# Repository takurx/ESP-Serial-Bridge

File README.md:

# ESP32-Serial-Bridge, ESP32S3-Serial-Bridge, 3 port concurrent

---

# Takurx's Notes

## Project Overview

This repository is a fork of [AlphaLima/ESP32-Serial-Bridge](https://github.com/AlphaLima/ESP32-Serial-Bridge) (via [Yuri's fork](https://github.com/yuri-rage/ESP32-Serial-Bridge)).  
It provides a transparent WiFi (TCP/UDP) ↔ multi-UART bridge, targeting both ESP32 and **ESP32-S3** boards.

In addition to the original/Yuri functionality, this fork adds:

- ESP32-S3 (PlatformIO) support for Bridge (Host) and Client
- 3-UART concurrent client (`Kerberos`)
- Hardware flow control (CTS/RTS) pin definitions
- Buffer size tuning for high-throughput stability
- Non-blocking TX with pending queue
- PCB design (KiCad) for ESP32 and ESP32-S3
- 3D-printable enclosure STL files
- Speed test scripts and result logs

---

## Repository Structure

```
ESP-Serial-Bridge/
├── ESP-Serial-Bridge/                        # Original Arduino IDE sketch (ESP32/ESP8266)
│   ├── ESP-Serial-Bridge.ino
│   └── config.h
│
├── ESP32-Serial-WiFi-Client/                 # Arduino IDE single-UART TCP/UDP Client (Yuri)
│   ├── ESP32-Serial-WiFi-Client.ino
│   └── client_config.h
│
├── ESP32-Serial-WiFi-Client-Kerberos/        # Arduino IDE 3-UART concurrent Client (ESP32)
│   ├── ESP32-Serial-WiFi-Client-Kerberos.ino
│   └── client_config.h
│
├── pio-ESP32S3-Serial-WiFi-Bridge/           # PlatformIO Bridge (Host) for ESP32-S3
│   ├── src/main.cpp
│   ├── include/config.h
│   └── platformio.ini
│
├── pio-ESP32S3-Serial-WiFi-Client-Kerberos/  # PlatformIO 3-UART Client (Kerberos) for ESP32-S3
│   ├── src/main.cpp
│   ├── include/client_config.h
│   └── platformio.ini
│
├── pcb_kicad/
│   ├── esp_serial_bridge_pcb/                # KiCad PCB for ESP32
│   └── esp32s3_serial_bridge_pcb/            # KiCad PCB for ESP32-S3 (Kerberos)
│
├── case_3dprint/                             # 3D-printable enclosure STL files
├── speed_test_script/                        # Python speed-test scripts and result logs
└── README.md
```

---

## Recent Updates (Takurx)

### English

#### **Near Full-Speed 3-Port Operation Achieved (Jun 2026)**
Applied buffer optimizations (developed for the Bridge/Host) to the Client (Kerberos) side.  
Result: all three UARTs now operate at **≈ 110,000–115,200 bps** in both directions simultaneously.

- Host → Client (×3 ports): ≈ **110,000 bps** (previously ≈ 13,000 bps)
- Client → Host (×3 ports): ≈ **115,200 bps** (stable)

Key changes:
- `setRxBufferSize(4096)` / `setTxBufferSize(4096)` applied to all UART ports before `begin()`
- Non-blocking TX: `availableForWrite()` used to avoid blocking `write()` calls
- Overflow data stored in a per-channel `txPendingBuf[]` queue and flushed next loop
- Bulk TCP read using `readBytes()` instead of byte-by-byte loop

#### **Buffer Separation: SOFTWAREBUFFERSIZE / HARDWAREBUFFERSIZE (Jun 2026)**
Separated buffer constant into two named constants in `config.h` for clarity:

| Constant | Size | Role |
|---|---|---|
| `HARDWAREBUFFERSIZE` | 4096 B | HardwareSerial internal ring buffer (ISR ← UART FIFO) |
| `SOFTWAREBUFFERSIZE` | 1024 B | Application working buffer (`buf1`, `buf2`, `txPending`) |

Data flow:
```
[UART RX] UART HW FIFO (1024B) → HardwareSerial ring buffer (4096B) → buf2[1024B] → TCP TX
[TCP RX]  TCP RX buffer (lwIP) → buf1[1024B] → HardwareSerial TX ring buffer (4096B) → UART TX
```

#### **pio-ESP32S3-Serial-WiFi-Client-Kerberos — 3-UART PlatformIO Client (Apr 2026)**
Added a PlatformIO version of the 3-UART concurrent client for ESP32-S3.  
Mirrors the same buffer/non-blocking approach as the Bridge Host side.

#### **PCB Design (KiCad) (Mar 2026)**
Added KiCad PCB designs (schematic + layout + Gerber) for:
- `esp_serial_bridge_pcb` — for ESP32 modules
- `esp32s3_serial_bridge_pcb` — for ESP32-S3 modules (Kerberos)

#### **pio-ESP32S3-Serial-WiFi-Bridge — ESP32-S3 PlatformIO Port (Feb 2026)**
New PlatformIO project targeting **RYMCU ESP32-S3-DevKitC-1** (board: `rymcu-esp32-s3-devkitc-1`).

Notable changes from original:
- All 3 UART ports configured with CTS/RTS pins (flow control disabled by default, can be enabled)
- `HARDWAREBUFFERSIZE` = 4096 bytes applied via `setRxBufferSize()` / `setTxBufferSize()`
- Non-blocking TX pending queue (`txPending[]`, `txPendingLen[]`) per UART port
- Bulk TCP read with `readBytes()` instead of 1-byte-at-a-time loop
- Hostname changed to `ESP32-S3`

#### **3-UART Concurrent Client — "Kerberos" (Feb 2026)**
Added `ESP32-Serial-WiFi-Client-Kerberos` (Arduino IDE) and its PlatformIO equivalent.  
Establishes three simultaneous TCP connections (one per UART) to the Bridge Host.

#### **Speed Test Results Summary**

| Date | Config | Host → Client | Client → Host |
|---|---|---|---|
| Dec 2025 | ESP32 AP mode, 1 port, flow ctrl None | ≈ 13,000 bps (drops to 7,000) | ≈ 100,000 bps (stable) |
| Feb 2026 | ESP32-S3 ↔ ESP32-S3, 1 port, flow ctrl ON | avg ≈ 82,000 bps | avg ≈ 20,000 bps |
| Feb 2026 | ESP32-S3 ↔ ESP32-S3, 1 port, flow ctrl OFF | avg ≈ 50,000 bps | avg ≈ 20,000 bps |
| Feb 2026 | ESP32-S3 ↔ ESP32-S3, 3 ports, flow ctrl None | 600–45,000 bps | 7,000–13,000 bps |
| Feb 2026 | 3 ports, flow ctrl ON/OFF | ≈ 13,000 bps avg | ≈ 10,000 bps avg |
| **Jun 2026** | **3 ports, buffer opt. applied to client**, flow ctrl None | **≈ 110,000 bps** | **≈ 115,200 bps** |

#### **Watch Dog Timer Bug Fix (Dec 2025)**
Fixed a critical bug where the system would enter an infinite loop when the Host side crashed and the Watch Dog Timer failed to activate. Now properly handles three scenarios:
1. Client-side crash (Client Reset) → Recovers with input from Host side
2. Host-side crash with quick recovery (Host Reset) → System continues normally
3. Host-side crash without recovery (Host OFF) → Client automatically resets every 30 seconds via Watch Dog Timer

#### **3D-Printable Case (Dec 2025)**
Added STL files for 3D-printable enclosure (box and cover, including v2 versions).

---

### 日本語

#### **3ポート同時フルスピード動作を達成 (2026年6月)**
Bridge（Host）側で開発したバッファ最適化手法をClient（Kerberos）側にも適用。  
全3ポートで**約110,000〜115,200 bps**の双方向同時通信が可能になった。

- Host → Client（×3ポート）: 約 **110,000 bps**（以前は約13,000 bps）
- Client → Host（×3ポート）: 約 **115,200 bps**（安定）

主な変更点：
- `setRxBufferSize(4096)` / `setTxBufferSize(4096)` を全UARTポートの `begin()` 前に適用
- 非ブロッキングTX: `availableForWrite()` でブロッキング `write()` を回避
- 書けなかったデータをポートごとの `txPendingBuf[]` キューに退避し次ループで再送
- TCPの一括読み出し（`readBytes()`）で1バイトずつのループを排除

#### **バッファ定数の分離: SOFTWAREBUFFERSIZE / HARDWAREBUFFERSIZE (2026年6月)**
`config.h` のバッファ定数を2つに分離して明確化：

| 定数 | サイズ | 役割 |
|---|---|---|
| `HARDWAREBUFFERSIZE` | 4096 B | HardwareSerial内部リングバッファ（ISR ← UART FIFO） |
| `SOFTWAREBUFFERSIZE` | 1024 B | アプリ作業バッファ（`buf1`, `buf2`, `txPending`） |

#### **pio-ESP32S3-Serial-WiFi-Client-Kerberos — 3UART PlatformIOクライアント (2026年4月)**
ESP32-S3向け3UART同時クライアントのPlatformIO版を追加。  
BridgeHost側と同じバッファ/非ブロッキング手法を適用。

#### **PCB設計（KiCad）(2026年3月)**
以下のKiCad PCB設計（回路図 + レイアウト + Gerber）を追加：
- `esp_serial_bridge_pcb` — ESP32モジュール用
- `esp32s3_serial_bridge_pcb` — ESP32-S3モジュール（Kerberos）用

#### **pio-ESP32S3-Serial-WiFi-Bridge — ESP32-S3 PlatformIO移植 (2026年2月)**
ESP32-S3（RYMCU ESP32-S3-DevKitC-1）向けの新しいPlatformIOプロジェクト。

主な変更点：
- 全3 UARTポートにCTS/RTSピンを定義（デフォルトはフロー制御無効）
- `HARDWAREBUFFERSIZE` = 4096バイトをRX/TXバッファ両方に適用
- ポートごとの非ブロッキング送信保留キュー（`txPending[]`）を実装
- TCP一括読み出しに変更（`readBytes()` 使用）
- ホスト名を `ESP32-S3` に変更

#### **3UART同時クライアント「Kerberos」(2026年2月)**
3つのTCP接続を同時確立するクライアント `ESP32-Serial-WiFi-Client-Kerberos`（Arduino IDE版）とそのPlatformIO版を追加。

#### **速度テスト結果サマリ**

| 日付 | 構成 | Host → Client | Client → Host |
|---|---|---|---|
| 2025年12月 | ESP32 APモード、1ポート、フロー制御なし | 約13,000 bps（時々7,000に低下） | 約100,000 bps（安定） |
| 2026年2月 | ESP32-S3同士、1ポート、フロー制御あり | 平均 約82,000 bps | 平均 約20,000 bps |
| 2026年2月 | ESP32-S3同士、1ポート、フロー制御なし | 平均 約50,000 bps | 平均 約20,000 bps |
| 2026年2月 | ESP32-S3同士、3ポート同時、フロー制御なし | 600〜45,000 bps | 7,000〜13,000 bps |
| 2026年2月 | 3ポート、フロー制御あり/なし | 平均 約13,000 bps | 平均 約10,000 bps |
| **2026年6月** | **3ポート、クライアント側バッファ最適化適用後**、フロー制御なし | **約110,000 bps** | **約115,200 bps** |

#### **Watch Dog Timer バグ修正 (2025年12月)**
Host側が落ちた時に無限ループに陥り、Watch Dog Timerが効かなかった重大なバグを修正。以下の3つのケースに対応:
1. Client側が落ちた場合（ClientのReset）→ Host側からの入力で回復
2. Host側が落ちてすぐ回復した場合（HostのReset）→ 正常動作
3. Host側が落ちて回復しない場合（HostのOFF）→ 30秒ごとにWatch Dog TimerでClientを自動Reset

#### **3Dプリント用ケース (2025年12月)**
3Dプリント可能なケースのSTLファイルを追加（ボックスとカバー、v2バージョンを含む）。

---

## Hardware: ESP32-S3 Pin Assignment

### Bridge Host (`pio-ESP32S3-Serial-WiFi-Bridge`)

| Port | RX Pin | TX Pin | CTS Pin | RTS Pin | TCP Port | UDP Port |
|---|---|---|---|---|---|---|
| COM0 | GPIO1 | GPIO43 | GPIO16 | GPIO15 | 8880 | 14550 |
| COM1 | GPIO18 | GPIO17 | GPIO10 | GPIO9  | 8881 | 14551 |
| COM2 | GPIO38 | GPIO37 | GPIO36 | GPIO35 | 8882 | 14552 |

- Static IP (AP mode): `192.168.4.1`
- Default SSID: `ssid_esp_uart_bridge3x3`
- Hardware flow control: pins defined, **disabled by default** (comment in code to enable)

---

# Yuri's Notes

This fork is compatible with both the ESP32 and ESP8266.

Because the ESP8266 has some idiosyncrasies with its hardware serial ports, I used SoftwareSerial to implement the ESP8266 bridge.  It is limited to ~115200 baud and will likely prove less reliable than an ESP32. `BLUETOOTH` (hardware limitation) and `PROTOCOL_UDP` (software limitation) are not available on the ESP8266.

As is, the sketch will compile, build, and upload without errors for the ESP32.  Edit `config.h` to configure and build for ESP8266.

There are many configurable parameters in `config.h`. Edit to suit your needs - inline comments should provide clarity.

## Major update, Apr 2023:
* Fixed compatibility with Arduino framework 2.0
* Added compatibility with PlatformIO.
* Implemented `PROTOCOL_UDP` (UDP broadcast)
* `PROTOCOL_TCP` and `PROTOCOL_UDP` can be used simultaneously, though doing so may result in serial traffic conflicts if your client connections are not managed carefully.
* Added `ESP32-Serial-WiFi-Client.ino` in a separate sketch folder to make an ESP32 TCP or UDP client that connects to the ESP-Serial-Bridge. Edit `client_config.h` and upload to a second board.
* Multiple bugs (possible buffer overruns) are fixed in the latest commit(s).
* Latest commits also include some styling/readability edits, though I can easily admit that it isn't the "prettiest" of C++ projects.

---

# ESP32-Serial-Bridge (Original by AlphaLima)

Transparent WiFi (TCP) to all three UART Bridge, supports both AP and STATION WiFi modes. The .ino file is the code for the ESP32. Use Arduino IDE for ESP32 to compile and upload it to the ESP32.
I made this project in order to connect Flight equipment devices devices like (Radio, Vario FLARM), to a Flight Computer (Kobo, Smartphones etc.),  but it is not limited to that. You can use it wherever you want, but on your own risk. Read license file for more details.                                  

===============================================================

Used Libraries: (must be installed in the arduino IDE):

https://github.com/espressif/arduino-esp32

===============================================================

In some cases the memorylayout is to small for this scetch.
If you face this problem you can either disable Bluetooth by removing
#define BLUETOOTH
in config.h 
or change the partition size as described here:
https://desire.giesecke.tk/index.php/2018/04/20/change-partition-size-arduino-ide/

Arduino hardware configuration:

https://github.com/AlphaLima/ESP32-Serial-Bridge/blob/master/Settings.jpg

===============================================================

example usecases:

https://www.youtube.com/watch?v=K2Hia06IMtk

https://www.youtube.com/watch?v=GoSxlQvuAhg

# Hardware (Original ESP32)
here is the wiring diagram recomendation:
https://raw.githubusercontent.com/AlphaLima/ESP32-Serial-Bridge/master/ESP32-SerialBridge.jpg             
Pinning                                                                                     
COM0 Rx <-> GPIO21                                                                               
COM0 Tx <-> GPIO01                                                                                 
COM1 Rx <-> GPIO16                                                                               
COM1 Tx <-> GPIO17                                                                              
COM2 Rx <-> GPIO15                                                                               
COM2 Tx <-> GPIO04                                                                              

NOTE: The PIN assignment has changed and may not look straigt forward (other PINs are marke as Rx/Tx), but this assignment allows to flash via USB also with hooked MAX3232 serial drivers.

I recomend to start your project with a Node32s or compatible evaluation board. For a TTL to RS232 level conversion search google for "TTL RS3232 Converter"

https://tech.scargill.net/wp-content/uploads/2017/05/ESP326.jpg

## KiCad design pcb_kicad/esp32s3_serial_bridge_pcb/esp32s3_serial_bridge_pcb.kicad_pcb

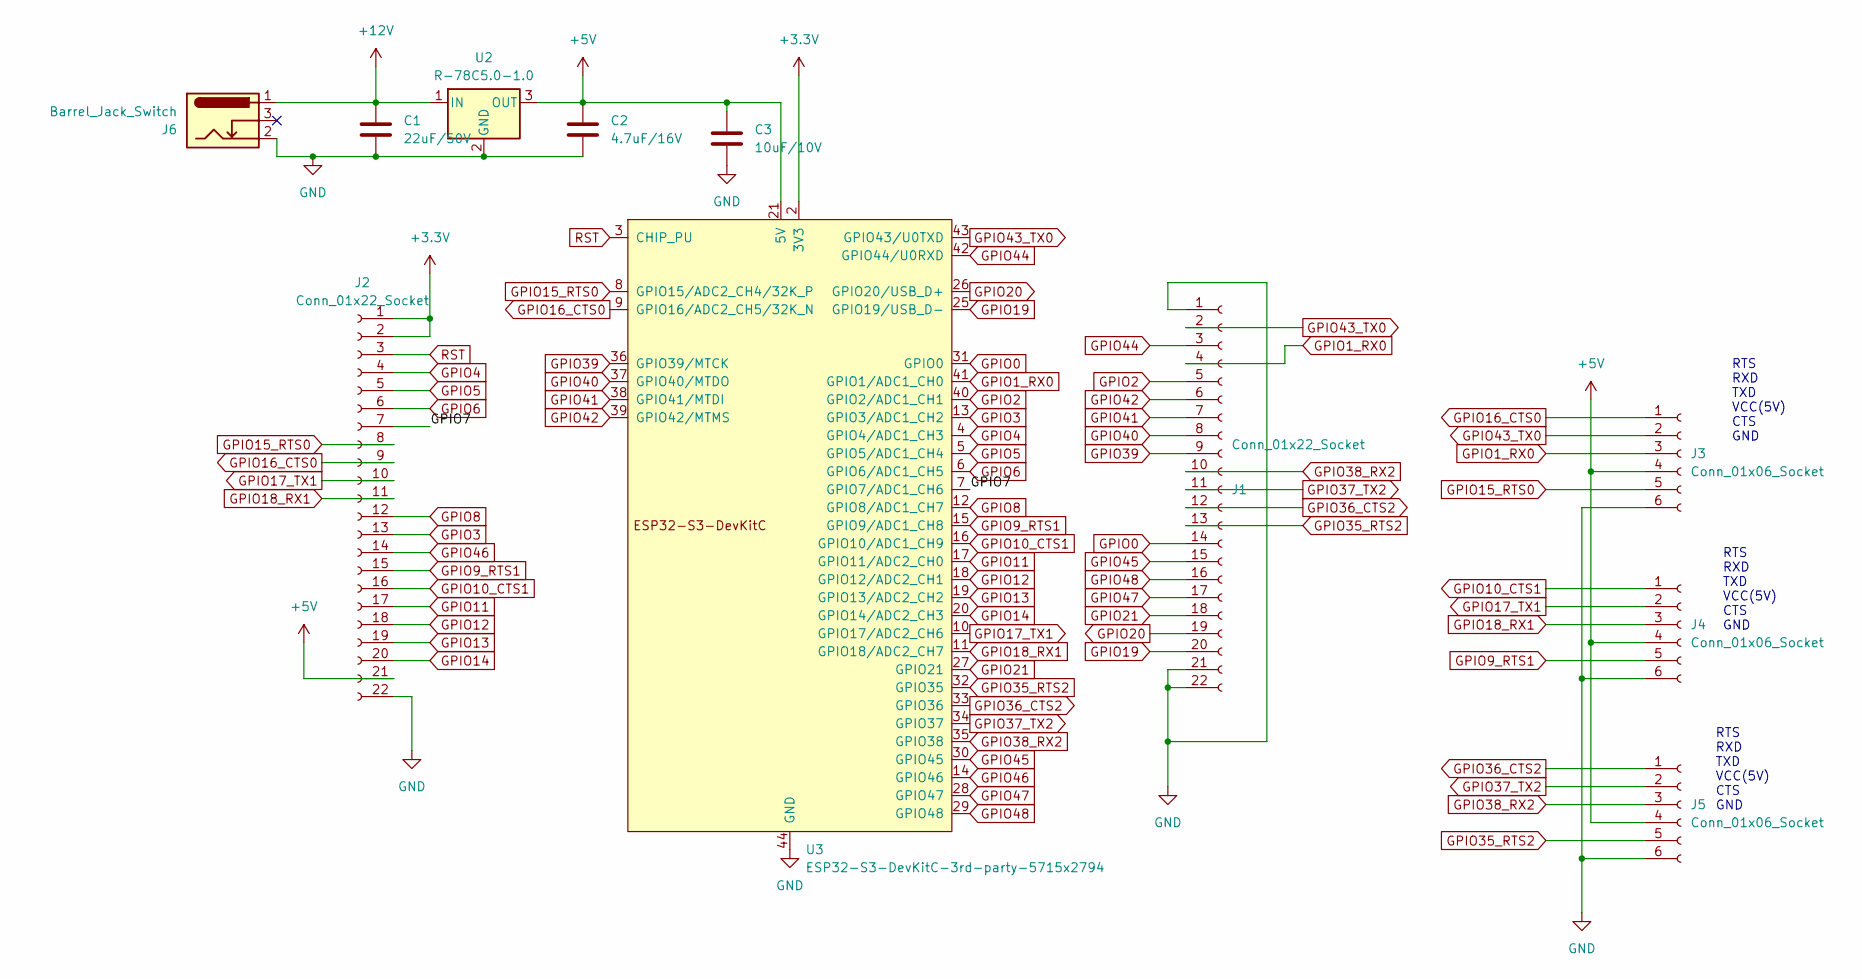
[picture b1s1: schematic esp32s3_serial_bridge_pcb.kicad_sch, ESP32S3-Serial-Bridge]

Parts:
C1: 22uF/50V; C_2220_5750Metric_Pad1.97x5.40mm_HandSolder
C2: 4.7uF/16V; C_1210_3225Metric_Pad1.33x2.70mm_HandSolder
C3: 10uF/10V; C_1210_3225Metric_Pad1.33x2.70mm_HandSolder
J1, J2: Conn_01x22_Socket; PinHeader_1x22_P2.54mm_Vertical
J3, J4, J5: Conn_01x06_Socket; PinHeader_1x06_P2.54mm_Vertical
J6: Barrel_Jack_Switch; BarrelJack_Horizontal
U2: R-78C5.0-1.0; Converter_DCDC_RECOM_R-78E-0.5_THT
U3: ESP32-S3-DevKitC-3rd-party-5715x2794; ESP32-S3-DevKitC_3rd_party_5715x2794

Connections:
+3.3V: J2.1, J2.2, U3.1 (3V3), U3.2 (3V3)
+5V: C2.1, C3.1, J2.21, J3.4, J4.4, J5.4, U2.3 (OUT), U3.21 (5V)
+12V: C1.1, J6.1, U2.1 (IN)
/GPIO7: J2.7, U3.7 (GPIO7/ADC1_CH6)
GND: C1.2, C2.2, C3.2, J1.1, J1.21, J1.22, J2.22, J3.6, J4.6, J5.6, J6.2, U2.2 (GND), U3.22 (GND), U3.23 (GND), U3.24 (GND), U3.44 (GND)
GPIO0: J1.14, U3.31 (GPIO0)
GPIO1_RX0: J1.4, J3.3, U3.41 (GPIO1/ADC1_CH0)
GPIO2: J1.5, U3.40 (GPIO2/ADC1_CH1)
GPIO3: J2.13, U3.13 (GPIO3/ADC1_CH2)
GPIO4: J2.4, U3.4 (GPIO4/ADC1_CH3)
GPIO5: J2.5, U3.5 (GPIO5/ADC1_CH4)
GPIO6: J2.6, U3.6 (GPIO6/ADC1_CH5)
GPIO8: J2.12, U3.12 (GPIO8/ADC1_CH7)
GPIO9_RTS1: J2.15, J4.5, U3.15 (GPIO9/ADC1_CH8)
GPIO10_CTS1: J2.16, J4.1, U3.16 (GPIO10/ADC1_CH9)
GPIO11: J2.17, U3.17 (GPIO11/ADC2_CH0)
GPIO12: J2.18, U3.18 (GPIO12/ADC2_CH1)
GPIO13: J2.19, U3.19 (GPIO13/ADC2_CH2)
GPIO14: J2.20, U3.20 (GPIO14/ADC2_CH3)
GPIO15_RTS0: J2.8, J3.5, U3.8 (GPIO15/ADC2_CH4/32K_P)
GPIO16_CTS0: J2.9, J3.1, U3.9 (GPIO16/ADC2_CH5/32K_N)
GPIO17_TX1: J2.10, J4.2, U3.10 (GPIO17/ADC2_CH6)
GPIO18_RX1: J2.11, J4.3, U3.11 (GPIO18/ADC2_CH7)
GPIO19: J1.20, U3.25 (GPIO19/USB_D-)
GPIO20: J1.19, U3.26 (GPIO20/USB_D+)
GPIO21: J1.18, U3.27 (GPIO21)
GPIO35_RTS2: J1.13, J5.5, U3.32 (GPIO35)
GPIO36_CTS2: J1.12, J5.1, U3.33 (GPIO36)
GPIO37_TX2: J1.11, J5.2, U3.34 (GPIO37)
GPIO38_RX2: J1.10, J5.3, U3.35 (GPIO38)
GPIO39: J1.9, U3.36 (GPIO39/MTCK)
GPIO40: J1.8, U3.37 (GPIO40/MTDO)
GPIO41: J1.7, U3.38 (GPIO41/MTDI)
GPIO42: J1.6, U3.39 (GPIO42/MTMS)
GPIO43_TX0: J1.2, J3.2, U3.43 (GPIO43/U0TXD)
GPIO44: J1.3, U3.42 (GPIO44/U0RXD)
GPIO45: J1.15, U3.30 (GPIO45)
GPIO46: J2.14, U3.14 (GPIO46)
GPIO47: J1.17, U3.28 (GPIO47)
GPIO48: J1.16, U3.29 (GPIO48)
RST: J2.3, U3.3 (CHIP_PU)

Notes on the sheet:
RTS RXD TXD VCC(5V) CTS GND

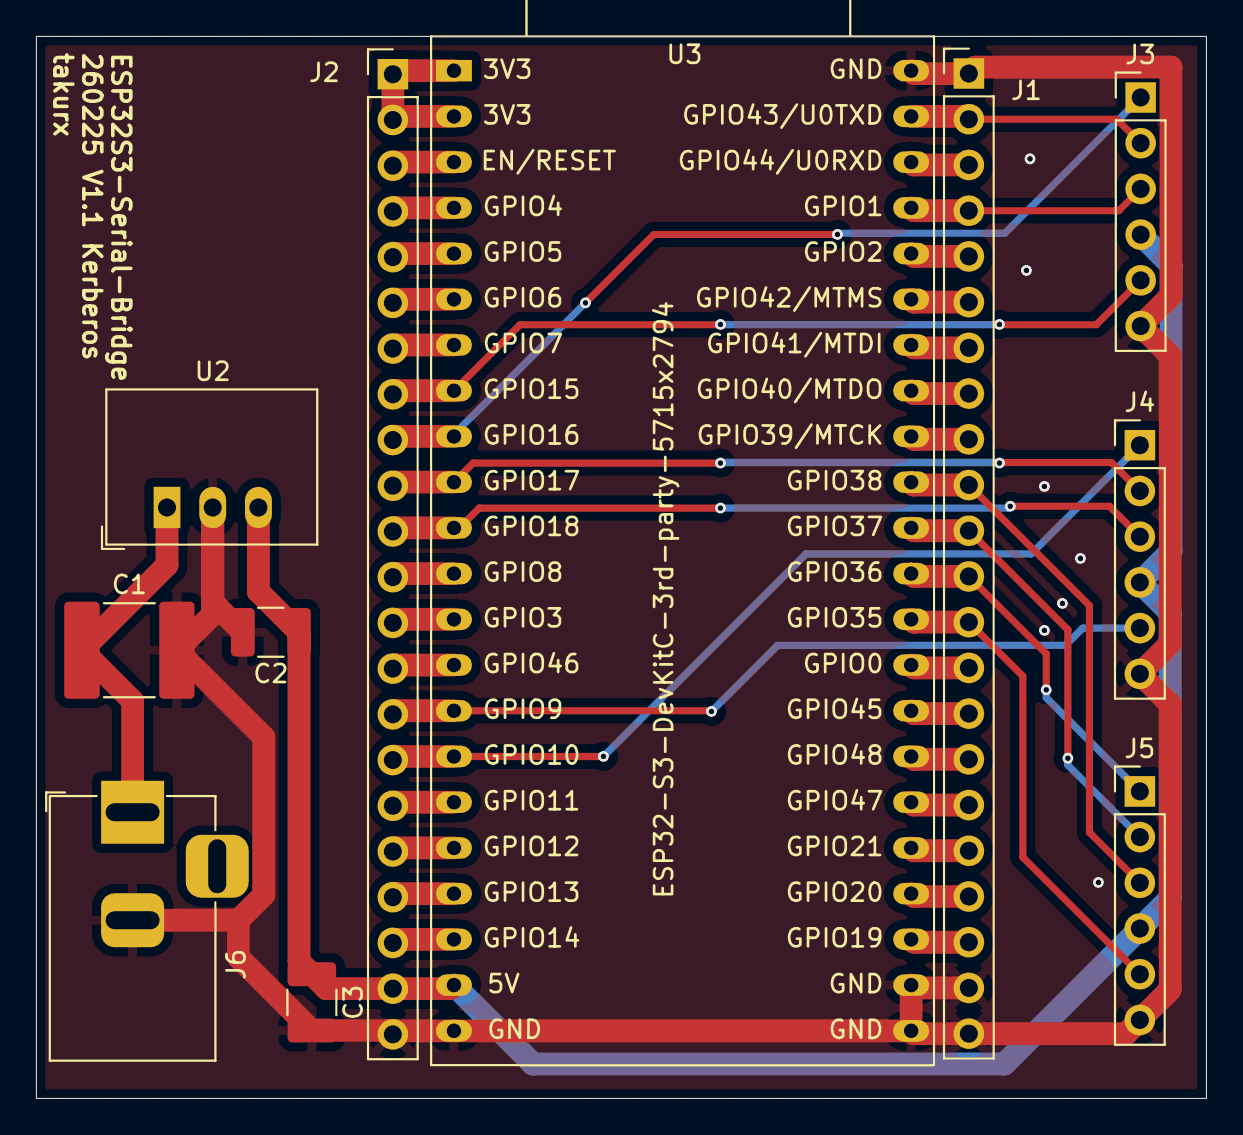
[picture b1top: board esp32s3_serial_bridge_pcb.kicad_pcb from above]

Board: 2 copper layers, 65.0 x 59.0 mm, 11 parts (0 on the bottom side), 41 nets.

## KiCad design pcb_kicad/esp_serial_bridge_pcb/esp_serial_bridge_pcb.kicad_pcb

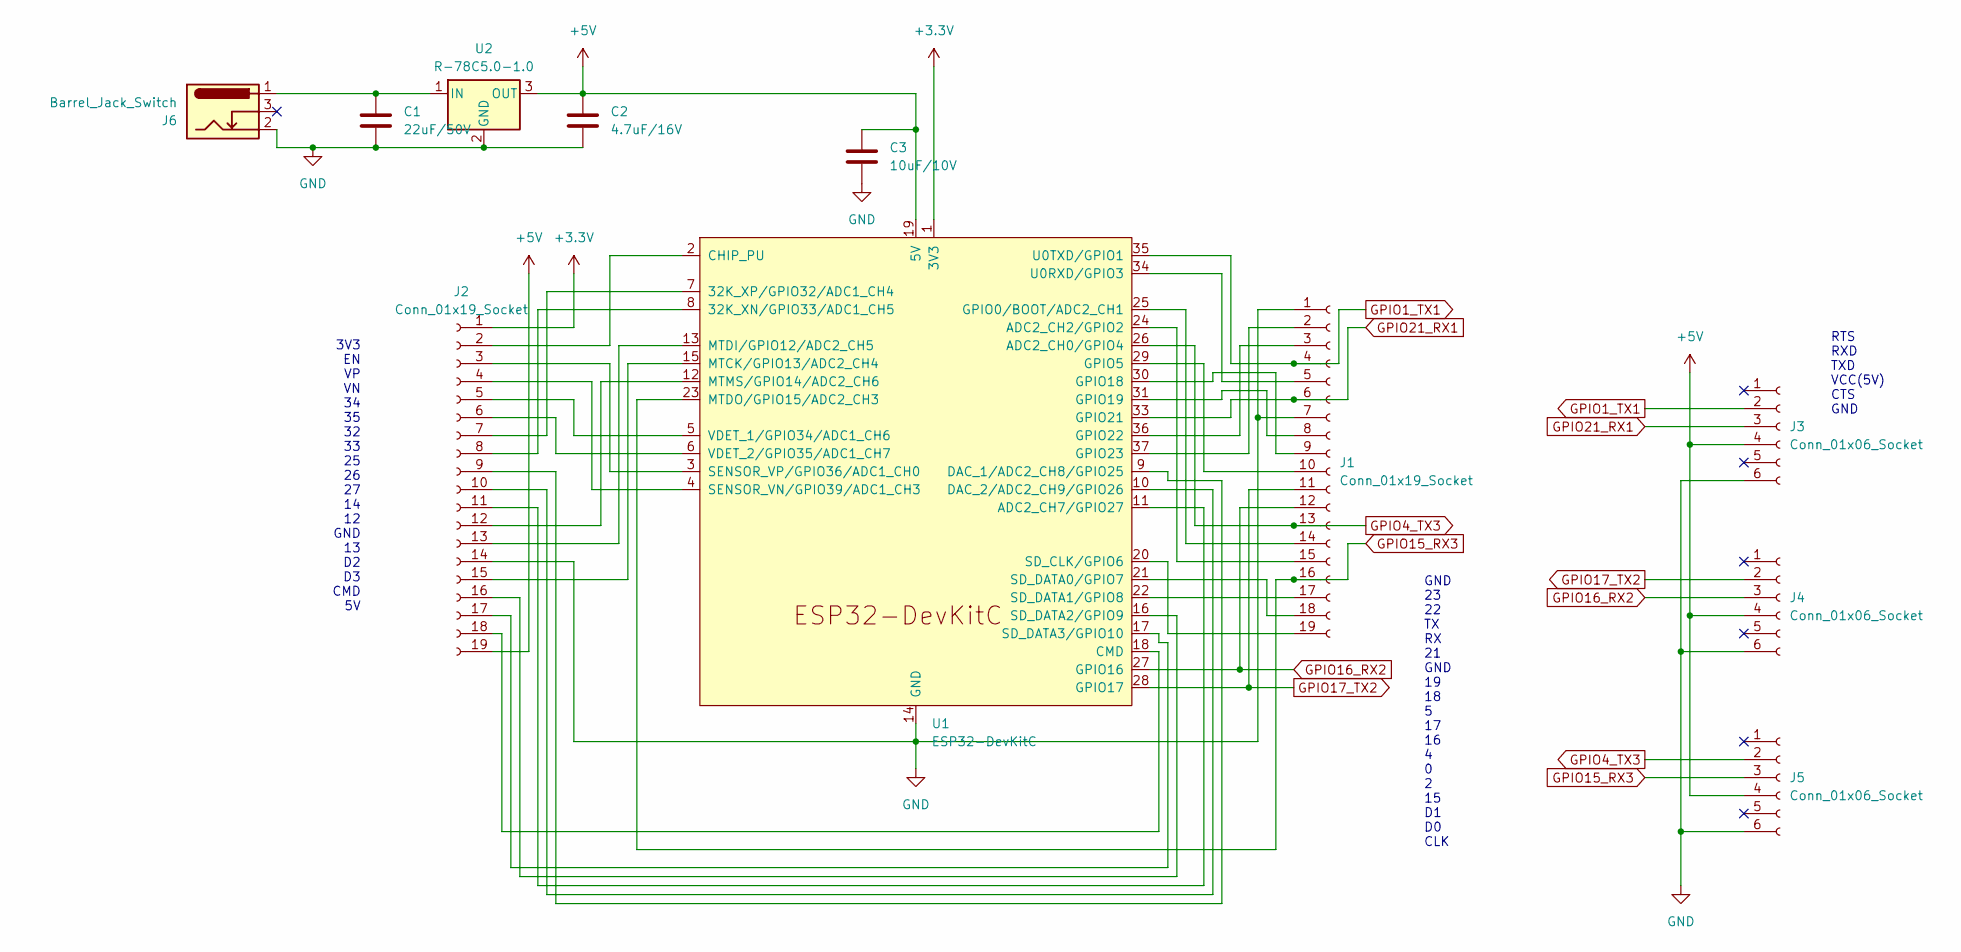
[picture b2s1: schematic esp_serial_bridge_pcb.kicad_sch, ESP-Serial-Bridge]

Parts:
C1: 22uF/50V; C_2220_5750Metric_Pad1.97x5.40mm_HandSolder
C2: 4.7uF/16V; C_1210_3225Metric_Pad1.33x2.70mm_HandSolder
C3: 10uF/10V; C_1210_3225Metric_Pad1.33x2.70mm_HandSolder
J1, J2: Conn_01x19_Socket; PinHeader_1x19_P2.54mm_Vertical
J3, J4, J5: Conn_01x06_Socket; PinHeader_1x06_P2.54mm_Vertical
J6: Barrel_Jack_Switch; BarrelJack_Horizontal
U1: ESP32-DevKitC
U2: R-78C5.0-1.0; Converter_DCDC_RECOM_R-78E-0.5_THT

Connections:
+3.3V: J2.1, U1.1 (3V3)
+5V: C2.1, C3.1, J2.19, J3.4, J4.4, J5.4, U1.19 (5V), U2.3 (OUT)
GND: C1.2, C2.2, C3.2, J1.1, J1.7, J2.14, J3.6, J4.6, J5.6, J6.2, U1.14 (GND), U1.32 (GND), U1.38 (GND), U2.2 (GND)
GPIO1_TX1: J1.4, J3.2, U1.35 (U0TXD/GPIO1)
GPIO4_TX3: J1.13, J5.2, U1.26 (ADC2_CH0/GPIO4)
GPIO15_RX3: J1.16, J5.3, U1.23 (MTDO/GPIO15/ADC2_CH3)
GPIO16_RX2: J1.12, J4.3, U1.27 (GPIO16)
GPIO17_TX2: J1.11, J4.2, U1.28 (GPIO17)
GPIO21_RX1: J1.6, J3.3, U1.33 (GPIO21)
unnamed: J1.2, U1.37 (GPIO23)
unnamed: J1.3, U1.36 (GPIO22)
unnamed: J1.5, U1.34 (U0RXD/GPIO3)
unnamed: J1.8, U1.31 (GPIO19)
unnamed: J1.9, U1.30 (GPIO18)
unnamed: J1.10, U1.29 (GPIO5)
unnamed: J1.14, U1.25 (GPIO0/BOOT/ADC2_CH1)
unnamed: J1.15, U1.24 (ADC2_CH2/GPIO2)
unnamed: J1.17, U1.22 (SD_DATA1/GPIO8)
unnamed: J1.18, U1.21 (SD_DATA0/GPIO7)
unnamed: J1.19, U1.20 (SD_CLK/GPIO6)
unnamed: J2.2, U1.2 (CHIP_PU)
unnamed: J2.3, U1.3 (SENSOR_VP/GPIO36/ADC1_CH0)
unnamed: J2.4, U1.4 (SENSOR_VN/GPIO39/ADC1_CH3)
unnamed: J2.5, U1.5 (VDET_1/GPIO34/ADC1_CH6)
unnamed: J2.6, U1.6 (VDET_2/GPIO35/ADC1_CH7)
unnamed: J2.7, U1.7 (32K_XP/GPIO32/ADC1_CH4)
unnamed: J2.8, U1.8 (32K_XN/GPIO33/ADC1_CH5)
unnamed: J2.9, U1.9 (DAC_1/ADC2_CH8/GPIO25)
unnamed: J2.10, U1.10 (DAC_2/ADC2_CH9/GPIO26)
unnamed: J2.11, U1.11 (ADC2_CH7/GPIO27)
unnamed: J2.12, U1.12 (MTMS/GPIO14/ADC2_CH6)
unnamed: J2.13, U1.13 (MTDI/GPIO12/ADC2_CH5)
unnamed: J2.15, U1.15 (MTCK/GPIO13/ADC2_CH4)
unnamed: J2.16, U1.16 (SD_DATA2/GPIO9)
unnamed: J2.17, U1.17 (SD_DATA3/GPIO10)
unnamed: J2.18, U1.18 (CMD)
unnamed: C1.1, J6.1, U2.1 (IN)

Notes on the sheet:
GND 23 22 TX RX 21 GND 19 18 5 17 16 4 0 2 15 D1 D0 CLK
3V3 EN VP VN 34 35 32 33 25 26 27 14 12 GND 13 D2 D3 CMD 5V
RTS RXD TXD VCC(5V) CTS GND

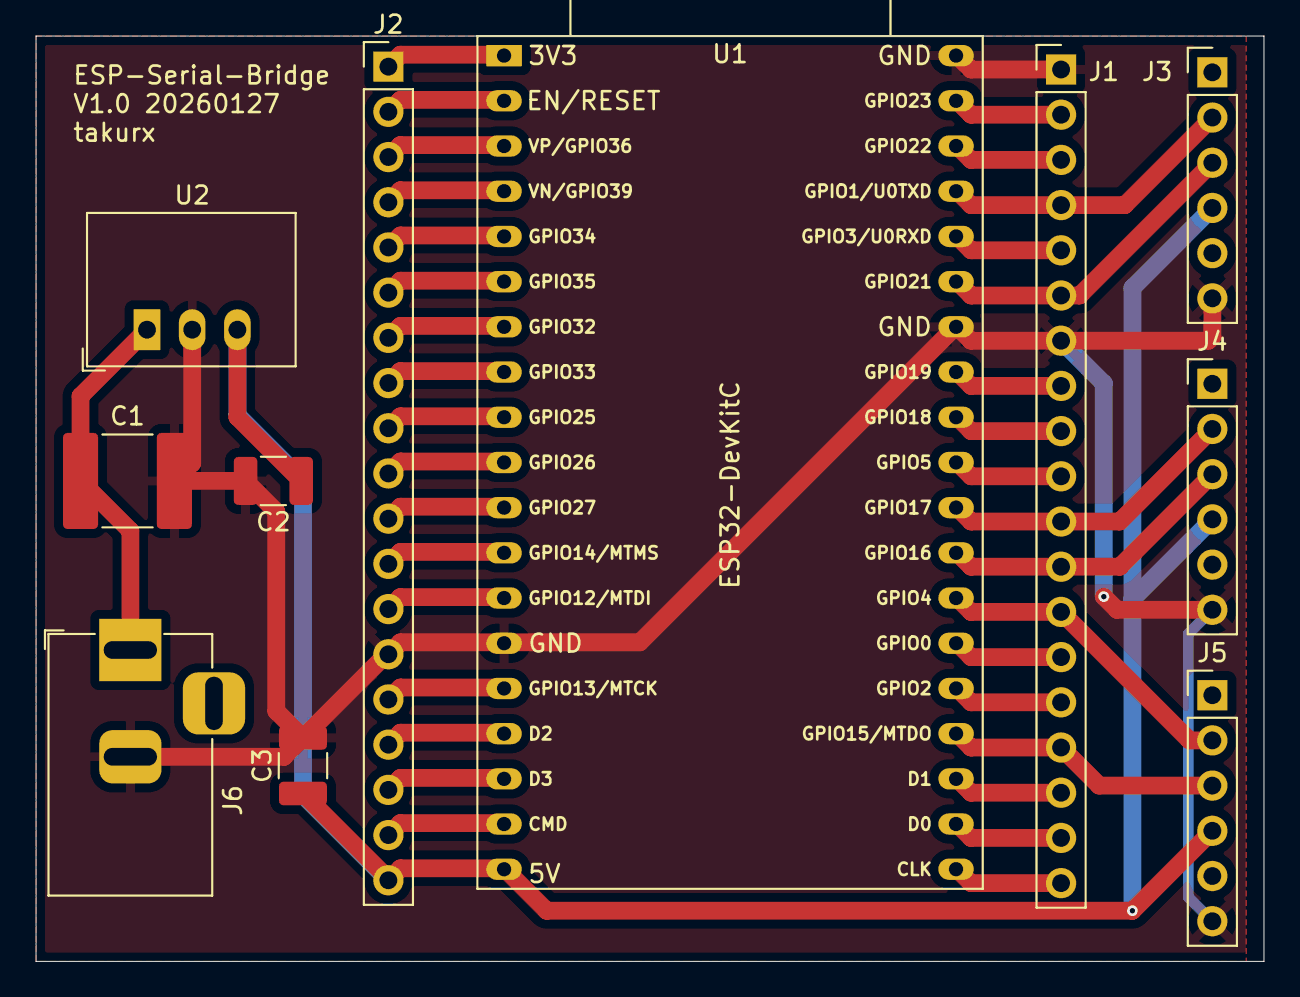
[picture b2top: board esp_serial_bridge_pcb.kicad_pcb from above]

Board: 2 copper layers, 69.0 x 52.0 mm, 11 parts (0 on the bottom side), 37 nets.

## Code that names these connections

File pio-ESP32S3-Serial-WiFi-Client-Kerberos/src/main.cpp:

/*
  pio-ESP32S3-Serial-WiFi-Client-Kerberos (3x UART concurrent bridge)
  - Makes 3 TCP client connections (one per UART) to ESP-Serial-Bridge server
  - Bridges UART0/UART1/UART2 <-> TCP sockets concurrently (non-blocking)

  Adjusted by takurx and Generated by ChatGPT 5.2

  Notes:
  - UART0 is usually used for USB programming/logging; using it for external RX/TX may affect uploads.
    The pin assignment below matches the repo README wiring suggestion:
      COM0 Rx <-> GPIO01, COM0 Tx <-> GPIO43, COM0 CTS <-> GPIO16, COM0 RTS <-> GPIO15
      COM1 Rx <-> GPIO18, COM1 Tx <-> GPIO17, COM1 CTS <-> GPIO10, COM1 RTS <-> GPIO09
      COM2 Rx <-> GPIO38, COM2 Tx <-> GPIO37, COM2 CTS <-> GPIO36, COM2 RTS <-> GPIO35
    (from repository README)  :contentReference[oaicite:1]{index=1}

  - If you want to keep USB Serial for logs, consider:
      * Use UART1 + UART2 + (SoftwareSerial) as 3rd, or
      * Move COM0 away from UART0 pins and use HardwareSerial(1/2) + an extra via IO matrix (advanced).
*/

#include <Arduino.h>
#include <WiFi.h>
#include <WiFiClient.h>
#include "client_config.h"

// -------- UART definitions --------
struct UartBridge {
  HardwareSerial* ser;
  int uart_num;
  int rx_pin;
  int tx_pin;
  int cts_pin;
  int rts_pin;
  uint32_t baud;
  bool invert;
};

// Default pinning from repo README (COM0/1/2)
static UartBridge UARTS[3] = {
  { &Serial,  0, UART0_RX_PIN, UART0_TX_PIN, UART0_CTS_PIN, UART0_RTS_PIN, UART0_BAUD, UART0_INVERT },
  { &Serial1, 1, UART1_RX_PIN, UART1_TX_PIN, UART1_CTS_PIN, UART1_RTS_PIN, UART1_BAUD, UART1_INVERT },
  { &Serial2, 2, UART2_RX_PIN, UART2_TX_PIN, UART2_CTS_PIN, UART2_RTS_PIN, UART2_BAUD, UART2_INVERT },
};

// -------- TCP clients --------
static WiFiClient clients[3];
static uint32_t lastReconnectMs[3] = {0, 0, 0};

// -------- TX pending queue (TCP->UART) --------
static uint8_t txPendingBuf[3][TX_PENDING_SIZE];
static size_t txPendingLen[3] = {0, 0, 0};

static inline bool connectClient(int i) {
  if (clients[i].connected()) return true;

  const uint32_t now = millis();
  if (now - lastReconnectMs[i] < RECONNECT_INTERVAL_MS) return false;
  lastReconnectMs[i] = now;

  clients[i].stop();
  bool ok = clients[i].connect(BRIDGE_HOST, BRIDGE_PORTS[i]);
  if (ok) {
    if (TCP_NODELAY) clients[i].setNoDelay(true);
    //if (CLIENT_KEEPALIVE_SEC > 0) clients[i].keepAlive(CLIENT_KEEPALIVE_SEC, CLIENT_KEEPALIVE_SEC, CLIENT_KEEPALIVE_SEC);
  }
  return ok;
}

static inline void pumpSerialToTcp(int i) {
  auto* s = UARTS[i].ser;
  auto& c = clients[i];
  if (!c.connected()) return;

  int avail = s->available();
  if (avail <= 0) return;

  uint8_t buf[TX_CHUNK];
  int n = s->readBytes(buf, (avail > (int)sizeof(buf)) ? sizeof(buf) : avail);
  if (n > 0) {
    c.write(buf, n);
  }
}

static inline void pumpTcpToSerial(int i) {
  auto* s = UARTS[i].ser;
  auto& c = clients[i];
  if (!c.connected()) return;

  // Flush any previously queued bytes first
  if (txPendingLen[i] > 0) {
    size_t writable = s->availableForWrite();
    if (writable > 0) {
      size_t toSend = min(writable, txPendingLen[i]);
      size_t sent = s->write(txPendingBuf[i], toSend);
      if (sent > 0) {
        txPendingLen[i] -= sent;
        if (txPendingLen[i] > 0) {
          memmove(txPendingBuf[i], txPendingBuf[i] + sent, txPendingLen[i]);
        }
      }
    }
  }

  int avail = c.available();
  if (avail <= 0) return;

  uint8_t buf[RX_CHUNK];
  int n = c.read(buf, (avail > (int)sizeof(buf)) ? sizeof(buf) : avail);
  if (n <= 0) return;

  // Write what fits immediately into the UART TX buffer
  size_t offset = 0;
  size_t writable = s->availableForWrite();
  if (writable > 0) {
    size_t immediate = min((size_t)n, writable);
    size_t sent = s->write(buf, immediate);
    offset = sent;
  }

  // Queue the remainder into txPendingBuf
  if (offset < (size_t)n) {
    size_t remaining = (size_t)n - offset;
    size_t freePending = TX_PENDING_SIZE - txPendingLen[i];
    size_t queued = min(remaining, freePending);
    if (queued > 0) {
      memcpy(txPendingBuf[i] + txPendingLen[i], buf + offset, queued);
      txPendingLen[i] += queued;
    }
  }
}

void setupUart(int i) {
  // Arduino-ESP32 allows inversion via begin() 6th arg in newer cores; to be safe, set later if needed.
  // UARTS[1], CTS 20 -> USB D-, RTS 19 -> USB D+ だと競合する気がするので、他のピンに割り当てたい -> UARTS[1], CTS 10, RTS 09 にした

  // Expand HW UART RX/TX buffers (must be called before begin())
  UARTS[i].ser->setRxBufferSize(HARDWARE_BUFFER_SIZE);
  UARTS[i].ser->setTxBufferSize(HARDWARE_BUFFER_SIZE);
  // Flow control disable
  UARTS[i].ser->begin(UARTS[i].baud, SERIAL_8N1, UARTS[i].rx_pin, UARTS[i].tx_pin, UARTS[i].invert);
  UARTS[i].ser->setHwFlowCtrlMode(UART_HW_FLOWCTRL_DISABLE); // TODO: flow control handling in software if needed
  pinMode(UARTS[i].cts_pin, OUTPUT); // CTS as input (not used if flow control disabled, but set to known state)
  pinMode(UARTS[i].rts_pin, OUTPUT); // RTS as output (not used if flow control disabled, but set to known state)
  digitalWrite(UARTS[i].cts_pin, LOW);
  digitalWrite(UARTS[i].rts_pin, LOW);
  UARTS[i].ser->setTimeout(0);

  /* // Flow control enable
  UARTS[i].ser->begin(UARTS[i].baud, SERIAL_8N1, UARTS[i].rx_pin, UARTS[i].tx_pin, UARTS[i].invert);
  UARTS[i].ser->setPins(UARTS[i].rx_pin, UARTS[i].tx_pin, UARTS[i].cts_pin, UARTS[i].rts_pin);
  UARTS[i].ser->setHwFlowCtrlMode(UART_HW_FLOWCTRL_CTS_RTS);
  UARTS[i].ser->setTimeout(0);
  */
}

void setupWifi() {
  WiFi.mode(WIFI_STA);
  WiFi.begin(WIFI_SSID, WIFI_PASS);

  const uint32_t t0 = millis();
  while (WiFi.status() != WL_CONNECTED) {
    delay(200);
    if (millis() - t0 > WIFI_CONNECT_TIMEOUT_MS) break;
  }
}

void setup() {
  // If you keep UART0 for external device, avoid using Serial for logging here.
  // If you keep USB logging, you must not steal UART0 pins.

#if ENABLE_USB_LOG
  Serial.begin(115200);
  delay(200);
#endif

  setupWifi();

  for (int i = 0; i < 3; i++) {
    setupUart(i);
  }

  // Initial connect attempts
  for (int i = 0; i < 3; i++) {
    connectClient(i);
  }
}

void loop() {
  // Ensure WiFi
  if (WiFi.status() != WL_CONNECTED) {
    // Try reconnect WiFi periodically
    static uint32_t lastWiFiTry = 0;
    uint32_t now = millis();
    if (now - lastWiFiTry > 2000) {
      lastWiFiTry = now;
      WiFi.disconnect(false);
      WiFi.begin(WIFI_SSID, WIFI_PASS);
    }
    //delay(10);
    return;
  }

  // Ensure TCP connections (3 sockets)
  for (int i = 0; i < 3; i++) {
    connectClient(i);
  }

  // Pump both directions for each UART
  for (int i = 0; i < 3; i++) {
    pumpSerialToTcp(i);
    pumpTcpToSerial(i);

    // If server closed the connection, stop() so reconnect logic can run cleanly
    if (clients[i].connected() && !clients[i].available() && !clients[i]) {
      clients[i].stop();
    }
  }

  // small yield to WiFi stack
  delay(1);
}

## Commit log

2025-10-07 tested UDP and TCP -> It is better TCP on my environment
    tested UDP and TCP -> It is better TCP on my environment
    - case of UDP
    Ok, Host -> Client communication
    Broken, Client -> Host communication
    - case of TCP
    Ok, bi-direction, Host -> Client and Client <- Host
2025-10-07 add speed test python code
    add speed test python code
2025-10-07 add result of speed test, Client -> Host, communication speed has limit?
    add result of speed test, Client -> Host, communication speed has limit?
    Client -> Host, communication speed has limitation? 80000 bps?
    0. same condition
    1. TCP only without UDP waiting -> same speed
    2. buffer size 1024 -> 2048, 80000 -> 77000 bps downed
2025-10-07 checking fastest speed......
    checking fastest speed......
2025-10-07 config.hを変えてみたりしたが変わらない
    config.hを変えてみたりしたが変わらない
    - Host -> Client, around 13000 bps, 1/10
    - Client -> Host, around 115200 bps
2025-10-08 test adding watch dog timer, wdt
    test adding watch dog timer, wdt
2025-12-17 Host側が落ちた時に無限ループかつWatch dog timerが効かなかったエラーを修正
    Host側が落ちた時に無限ループかつWatch dog timerが効かなかったエラーを修正
    1. Client側が落ちた場合（ClientのReset）→Host側からの入力で回復
    2. Host側が落ちてすぐ回復した場合（HostのReset）→OK
    3. Host側が落ちて回復しない場合（HostのOFF）→30sごとにWatch dog TimerでClientをReset
    の3ケースに対応した
2025-12-17 delete commented line
    delete commented line
2025-12-17 delete development memo
    delete development memo
2025-12-17 undo for pull request
    undo for pull request
2025-12-17 undo for pull request 2
    undo for pull request 2
2025-12-18 Ok, station mode and static IP address
    Ok, station mode and static IP address
2025-12-18 add speed test result, not better comparing AP mode
    add speed test result, not better comparing AP mode
    別途、外部Wi-Fiルータを用意したが、通信速度は改善しなかったところ
    Wi-Fiルータの設定を確認する必要はあるか
2025-12-18 add speed test result, not better comparing AP mode
    add speed test result, not better comparing AP mode
    static IP addressからrouterが認識してそうなDHCP IP addressにしてみた。
    AP modeと比較して通信速度は改善しなかったところ
    Static IP addressよりは良いかも
    まあAP modeで良いや
2025-12-18 add speed test result3, AP mode
    add speed test result3, AP mode
2025-12-19 change ssid
    change ssid
2025-12-19 add case, 3d printer
    add case, 3d printer
2026-01-27 update README with cline+claude sonnet 4.5
    update README with cline+claude sonnet 4.5
    >変更点を英語と日本語でREADME.mdの Takurx's Notesの章に箇条書きでまとめてみて
2026-01-27 add PCB ESP-Serial-Bridge V1.0
    add PCB ESP-Serial-Bridge V1.0
2026-01-27 add PCB ESP32S3-Serial-Bridge V1.0 (Working In Progress)
    add PCB ESP32S3-Serial-Bridge V1.0 (Working In Progress)
2026-01-28 add PCB ESP32S3-Serial-Bridge V1.0 Kerberos
    add PCB ESP32S3-Serial-Bridge V1.0 Kerberos
2026-02-10 add ESP32-Serial-WiFi-Client-Kerberos Bridge
    It is ESP32 x3 UART - ESP32 x3 UART, Wi-Fi Bridge and physical in/out put
2026-02-13 test kerberos to platfromio (not yet, work on board)
    test kerberos to platfromio (not yet, work on board)
2026-02-13 test Bridge (Host), not yet work on board
    test Bridge (Host), not yet work on board
2026-02-13 test client, not yet work on board
    test client, not yet work on board
2026-02-17 checked speed, working is ok, speed is enough?
    各3ポート115200bpsで乱数を送る設定で、
    Host x3→Client x3、各ポート600～45000 bps
    Host x3←Client x3、各ポート7000～13000 bps
2026-02-17 ESP32S3用に調整中......
    ESP32S3用に調整中......
2026-02-24 ok, working. fix serial begin function
    ok, working. fix serial begin function
2026-02-24 ひとまずHostのcom0だけflow controlを追加してみるテスト
    ひとまずHostのcom0だけflow controlを追加してみるテスト
2026-02-24 Hostのcom0, com2はOK
    Hostのcom0, com2はOK
    com1を変更するとdebugメッセージでなくなるのでピン配置を確認する
2026-02-24 CTS 20 -> USB D-, RTS 19 -> USB D+ で競合する気がするので、他のピンに割り当てたい
    CTS 20 -> USB D-, RTS 19 -> USB D+ で競合する気がするので、他のピンに割り当てたい
2026-02-24 client-kerberosの方もcom0, com2はOK, com1を回避した
    client-kerberosの方もcom0, com2はOK, com1を回避した
    com1のピン配置を変えてリトライする
2026-02-24 まずはflow controlあり
    まずはflow controlあり
2026-02-24 flow controlありの方が気持ち速そう
    flow controlあり
    host -> client, Average 82000 bps
    host <- client, Average 20000 bps
    flow controlなし
    host -> client, average 50000 bps
    host <- client, Average 20000 bps
2026-02-24 add summary
    add summary
2026-02-25 動作OK, CTS: GPIO20 -> 10, RTS: GPIO19 -> 9に変更
    動作OK, CTS: GPIO20 -> 10, RTS: GPIO19 -> 9に変更
    COM[1], CTS 20 -> USB D-, RTS 19 -> USB D+ だと競合して動作してない気がしたので
2026-02-25 client側はok
    client側はok
2026-02-25 ひとまずcom1なし
    ひとまずcom1なし
2026-02-25 hostもok
    hostもok
2026-02-25 動作ok
    動作ok
2026-02-25 PCBもCTS: GPIO20 -> 10, RTS: GPIO19 -> 9 に変更
    PCBもCTS: GPIO20 -> 10, RTS: GPIO19 -> 9 に変更
2026-02-26 flow 制御あり、3方向同時の通信速度テスト
    flow 制御あり、3方向同時の通信速度テスト
2026-02-26 add x3 speed test result
    add x3 speed test result
2026-02-26 flow controlありでpythonがctrl+cできたりできなかったりする
    host <- clientでhost側のserial.print出力があやしい気がする
    3ポートそろわないと出力出なかったり？してるかもで
2026-03-13 add case
    add case
2026-03-17 delete delay, move ESP-Serial-Bridge.ino to folder
    delete delay, move ESP-Serial-Bridge.ino to folder
2026-03-17 update comment
    update comment
2026-03-18 flow controlありだと、3ポートつながってRTS/CTSの操作がないと立ち上がらない
    flow controlありだと、3ポートつながってRTS/CTSの操作がないと立ち上がらない
    とくにpio-ESP32S3-Serial-WiFi-Bridgeの方、ポートオープンしないのは厳しい
    なので、基本はflow control disableにしておく
2026-03-19 adjust buffer size and delay
    adjust buffer size and delay
2026-03-19 flow controlなしにしたので、RTS/CTSのpin設定をcomment outした
    flow controlなしにしたので、RTS/CTSのpin設定をcomment outした
2026-03-19 buffer size 1024ぐらいが適切かも
    buffer size 1024ぐらいが適切かも
2026-03-27 念のためNo flow controlでもRTS, CTSを予定したピンをOUTPUT, LOWに
    念のためNo flow controlでもRTS, CTSを予定したピンをOUTPUT, LOWに
2026-03-27 回路をupdate
    回路をupdate
2026-03-27 serial flush interval from github copilot、問題解決にはちと違う気がする
    serial flush interval from github copilot、問題解決にはちと違う気がする
2026-03-27 ② TCP 読み込みを 1 バイトずつではなく一括に変更
    ② TCP 読み込みを 1 バイトずつではなく一括に変更
2026-03-27 新規TCPコネクション時にHardware Serial buffer をflushする、buffer sizeを明示化
    新規TCPコネクション時にHardware Serial buffer をflushする、buffer sizeを明示化
2026-03-27 test small chunk size
    test small chunk size
2026-03-27 add RAM and TX Queue
    add RAM and TX Queue
2026-04-02 add generated test script v2
    add generated test script v2
2026-04-02 add applied host transfer method to client, check yet
    add applied host transfer method to client, check yet
2026-04-02 add host buffer method
    add host buffer method
2026-06-12 speed test, result almost full speed 115200 bps
    speed test, result almost full speed 115200 bps
2026-06-16 add update command log with github copilot
    add update command log with github copilot
2026-06-16 add 4x3
    add 4x3
2026-06-16 update readme
    update readme
2026-06-23 Update project title in README.md
    Update project title in README.md
2026-06-23 Update speed test results with flow control details
    Update speed test results with flow control details
